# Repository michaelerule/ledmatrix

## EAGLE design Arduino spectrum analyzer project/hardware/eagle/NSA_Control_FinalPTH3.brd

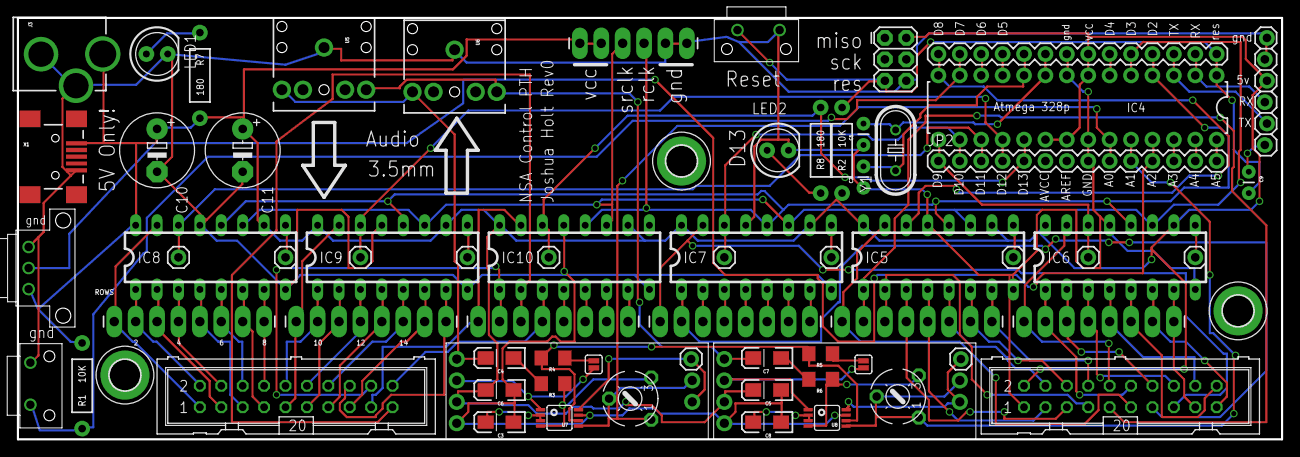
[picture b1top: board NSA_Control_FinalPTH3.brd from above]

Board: 2 copper layers, 150.0 x 50.0 mm, 72 parts (0 on the bottom side), 96 nets.

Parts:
C1, C2: 22pf; CAP-PTH-SMALL
C3, C4, C5, C6, C7, C8: 1uF; EIA3216-KIT
C9: 0.1uF; CAP-PTH-SMALL
C10, C11: E5-8,5
H1, H2, H3: MOUNT-PAD-ROUND3.6; 3,6-PAD
IC4: AVR-MEGA8-PZIF_SOCKET; DIL28-3-ZIF_SOCKET
IC5, IC6, IC7, IC8, IC9, IC10: 74LS595N; DIL16
J1: AVR_SPI_PRG_6PTH; 2X3
J3: POWER_JACKPTH_LOCK; POWER_JACK_PTH_LOCK
JP1, JP2: M14; 1X14
JP4: 1X06_LONGPADS
JP5, JP6, JP7, JP15, JP16, JP17, JP18, JP19, JP20, JP21, JP22, JP23: M01PTH; 1X01
JP8, JP9, JP11, JP12, JP13, JP14: 1X08_LONGPADS
JP10: 1X06_LOCK
LED1, LED2: LED5MM
R1, R2: 10K; AXIAL-0.4
R3, R6: 10K; 1206
R4, R5: 100K; 1206
R7, R8: 180; AXIAL-0.4
SJ1, SJ2: SOLDERJUMPERNC; SJ_2S
SV1, SV2: ML20
TM1, TM2: 200K; 6MM
U5, U6: AUDIO-JACK
U7, U8: LM4889_MSOP; MSOP8
U$1, U$5: TE_RA_SWTICH; TE_RA_SWITCH
U$6, U$7: MD_AMP
U$10: RK09L
X1: USBSMD; USB-MINIB
Y1: HC49U-V

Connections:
6V: R4.2, R5.2, U7.6, U8.6
A0: IC4.23, JP2.9, TM1.A, TM1.S, U7.5, U$6.SP2
A1: IC4.24, JP2.10, TM2.A, TM2.S, U8.5, U$7.SP2
A2: IC4.25, JP2.11, U$10.P$2
A3: IC4.26, JP2.12
A4: IC4.27, JP2.13
A5: IC4.28, JP2.14
BTN: IC4.13, JP1.13, R1.P$1, U$5.P$2
COL1: IC5.15, JP8.1, SV1.11
COL2: IC5.1, JP8.2, SV1.9
COL3: IC5.2, JP8.3, SV1.7
COL4: IC5.3, JP8.4, SV1.5
COL5: IC5.4, JP8.5, SV1.3
COL6: IC5.5, JP8.6, SV1.4
COL7: IC5.6, JP8.7, SV1.6
COL8: IC5.7, JP8.8, SV1.8
COL9: IC6.15, JP9.1, SV1.10
COL10: IC6.1, JP9.2, SV1.12
COL11: IC6.2, JP9.3, SV1.14
COL12: IC6.3, JP9.4, SV1.16
COL13: IC6.4, JP9.5, SV1.18
COL14: IC6.5, JP9.6, SV1.20
COL15: IC6.6, JP9.7, SV1.19
COL16: IC6.7, JP9.8, SV1.17
COL17: IC7.15, JP11.1, SV1.15
COL18: IC7.1, JP11.2, SV1.13
D4: IC4.6, JP1.6
D5: IC4.11, JP1.11
D6: IC4.12, JP1.12
DTR: C9.1, JP10.1
GND: C1.1, C2.1, C3.C, C5.C, C6.C, C8.C, C10.-, C11.-, IC4.8, IC4.22, IC5.8, IC5.13, IC6.8, IC6.13, IC7.8, IC7.13, IC8.8, IC8.13, IC9.8, IC9.13, IC10.8, IC10.13, J1.6, J3.GND, J3.GNDBREAK, JP1.8, JP2.8, JP4.1, JP4.2, JP10.5, JP10.6, LED1.K, LED2.K, SV1.1, U5.SLEEVE, U6.SLEEVE, U7.7, U8.7, U$1.P$1, U$5.P$1, U$6.GND, U$7.GND, U$10.P$1, X1.GND
L_IN: C4.A, U5.TIP, U6.TIP, U$6.AIN
unnamed: IC7.4, JP11.5
unnamed: IC7.5, JP11.6
unnamed: IC7.6, JP11.7
unnamed: IC7.7, JP11.8
unnamed: IC10.4, JP14.5
unnamed: IC10.5, JP14.6
unnamed: LED1.A, R7.P$1
unnamed: LED2.A, R8.P$1
unnamed: IC10.6, JP14.7
unnamed: C8.A, U8.2, U8.3
unnamed: IC5.9, JP5.1
unnamed: IC6.9, JP16.1
unnamed: IC10.7, JP14.8
unnamed: C3.A, U7.2, U7.3
unnamed: R6.1, TM2.E, U8.4
unnamed: R3.1, TM1.E, U7.4
unnamed: C4.C, R3.2
unnamed: C7.C, R6.2
unnamed: R4.1, SJ1.2
unnamed: R5.1, SJ2.2
unnamed: IC7.2, JP11.3
unnamed: IC7.3, JP11.4
unnamed: IC7.9, JP18.1
unnamed: IC8.9, JP20.1
unnamed: IC9.9, JP22.1
RCLK: IC4.4, IC5.12, IC6.12, IC7.12, IC8.12, IC9.12, IC10.12, JP1.4, JP4.3
RES: C9.2, IC4.1, J1.5, JP1.1, R2.P$1, U$1.P$2
ROW1: IC8.15, JP12.1, SV2.1
ROW2: IC8.1, JP12.2, SV2.2
ROW3: IC8.2, JP12.3, SV2.3
ROW4: IC8.3, JP12.4, SV2.4
ROW5: IC8.4, JP12.5, SV2.5
ROW6: IC8.5, JP12.6, SV2.6
ROW7: IC8.6, JP12.7, SV2.7
ROW8: IC8.7, JP12.8, SV2.8
ROW9: IC9.15, JP13.1, SV2.9
ROW10: IC9.1, JP13.2, SV2.10
ROW11: IC9.2, JP13.3, SV2.11
ROW12: IC9.3, JP13.4, SV2.12
ROW13: IC9.4, JP13.5, SV2.13
ROW14: IC9.5, JP13.6, SV2.14
ROW15: IC9.6, JP13.7, SV2.15
ROW16: IC9.7, JP13.8, SV2.16
ROW17: IC10.15, JP14.1, SV2.17
ROW18: IC10.1, JP14.2, SV2.18
ROW19: IC10.2, JP14.3, SV2.19
ROW20: IC10.3, JP14.4, SV2.20
RX: IC4.2, JP1.2, JP10.3
R_IN: C7.A, U5.RING, U6.RING, U$7.AIN
SP1: JP6.1, U7.8, U$6.SP1
SP1_2: JP7.1, U8.8, U$7.SP1
SR1_SER: IC4.14, IC5.14, JP1.14
SR2_SER: IC4.15, IC6.14, JP2.1, JP15.1
SR3_SER: IC4.16, IC7.14, JP2.2, JP17.1
SR4_SER: IC4.17, IC8.14, JP2.3, JP19.1
SR5_SER: IC4.18, IC9.14, JP2.4, JP21.1
SR6_SER: IC4.19, IC10.14, JP2.5, JP23.1, R8.P$2
SRCLK: IC4.5, IC5.11, IC6.11, IC7.11, IC8.11, IC9.11, IC10.11, JP1.5, JP4.4
STDN: SJ1.1, U7.1, U$6.STDN
STDN2: SJ2.1, U8.1, U$7.STDN
TX: IC4.3, JP1.3, JP10.2
VCC: C5.A, C6.A, C10.+, C11.+, IC4.7, IC4.20, IC4.21, IC5.10, IC5.16, IC6.10, IC6.16, IC7.10, IC7.16, IC8.10, IC8.16, IC9.10, IC9.16, IC10.10, IC10.16, J1.2, J3.PWR, JP1.7, JP4.5, JP4.6, JP10.4, R1.P$2, R2.P$2, R7.P$2, SV1.2, U$6.5V, U$7.5V, U$10.P$3, X1.VBUS
XTAL1: C1.2, IC4.9, JP1.9, Y1.2
XTAL2: C2.2, IC4.10, JP1.10, Y1.1

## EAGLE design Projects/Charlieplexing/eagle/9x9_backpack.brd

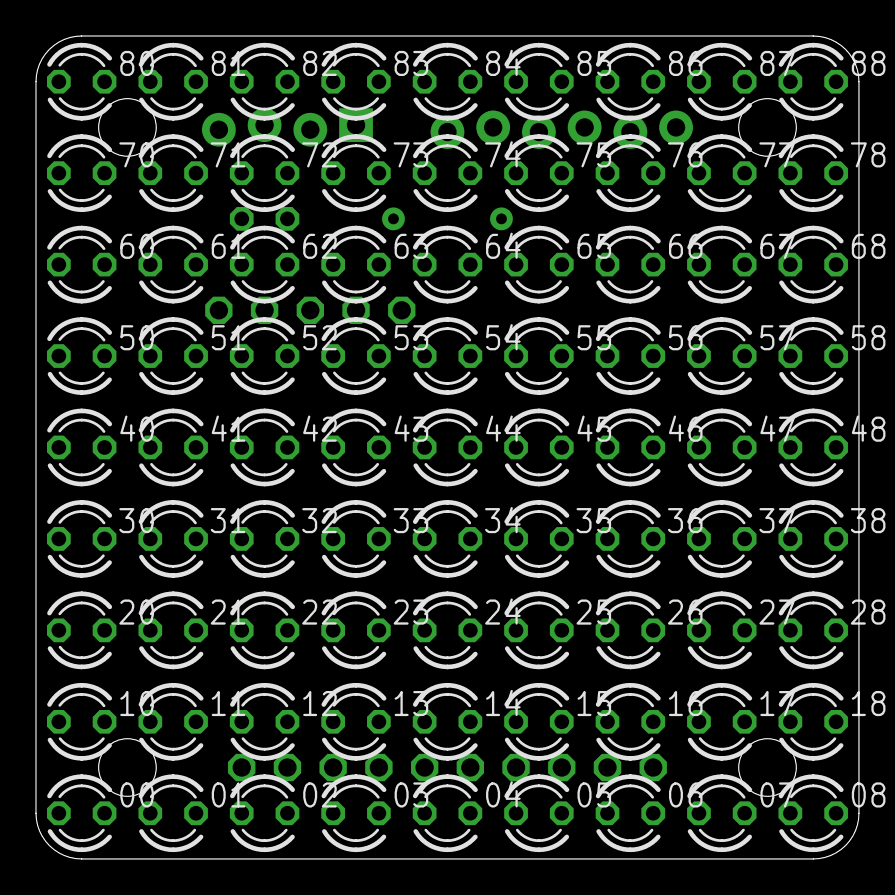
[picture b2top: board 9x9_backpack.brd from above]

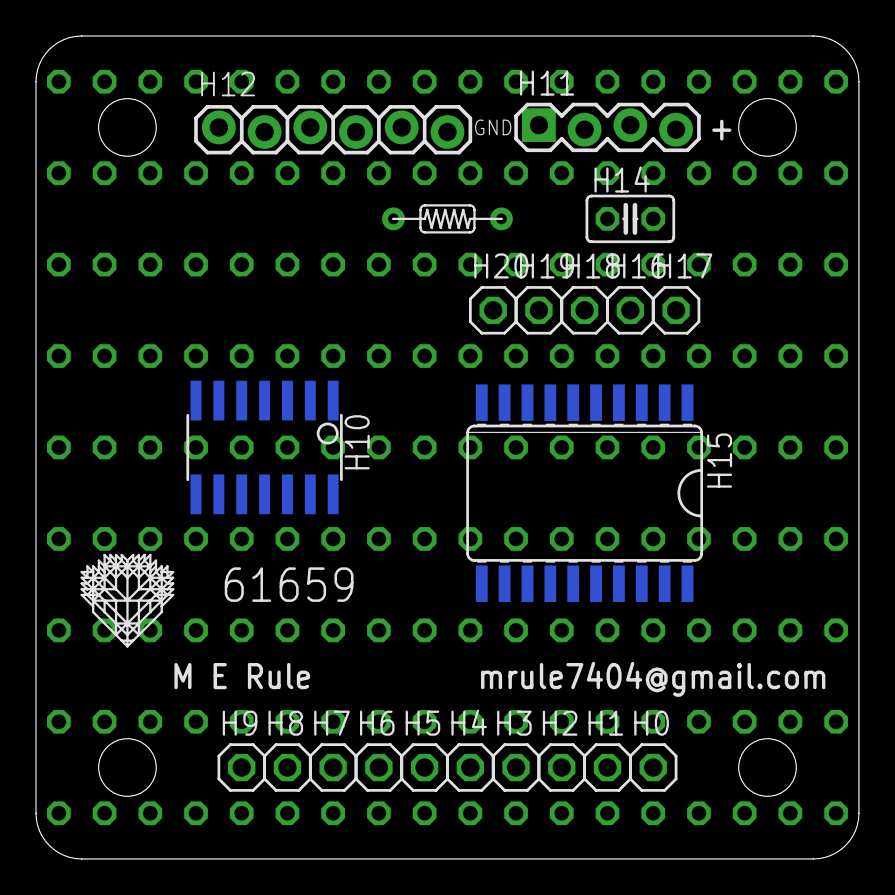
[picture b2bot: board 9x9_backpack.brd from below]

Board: 2 copper layers, 45.7 x 45.7 mm, 103 parts (22 on the bottom side), 20 nets, no tracks yet.

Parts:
00, 01, 02, 03, 04, 05, 06, 07, 08, 10, 11, 12, 13, 14, 15, 16, 17, 18, 20, 21, 22, 23, 24, 25, 26, 27, 28, 30, 31, 32, 33, 34, 35, 36, 37, 38, 40, 41, 42, 43, 44, 45, 46, 47, 48, 50, 51, 52, 53, 54, 55, 56, 57, 58, 60, 61, 62, 63, 64, 65, 66, 67, 68, 70, 71, 72, 73, 74, 75, 76, 77, 78, 80, 81, 82, 83, 84, 85, 86, 87, 88: LED3MM
H0, H1, H2, H3, H4, H5, H6, H7, H8, H9, H16, H17, H18, H19, H20: 1X01
H10: SOIC14
H11: 1X04_LOCK
H12: 1X06_LOCK
H13: R-6
H14: C025-025X050
H15: SO20L
H21: LOGO

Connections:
D: 00.A, 11.A, 22.A, 33.A, 44.A, 55.A, 66.A, 77.A, 88.A, H9.1, H10.8, H12.5, H15.18
S0: 00.K, 01.A, 02.A, 03.A, 04.A, 05.A, 06.A, 07.A, 08.A, 10.K, 20.K, 30.K, 40.K, 50.K, 60.K, 70.K, 80.K, H0.1, H10.3, H15.9
S1: 01.K, 10.A, 11.K, 12.A, 13.A, 14.A, 15.A, 16.A, 17.A, 18.A, 21.K, 31.K, 41.K, 51.K, 61.K, 71.K, 81.K, H1.1, H10.5, H15.16
S2: 02.K, 12.K, 20.A, 21.A, 22.K, 23.A, 24.A, 25.A, 26.A, 27.A, 28.A, 32.K, 42.K, 52.K, 62.K, 72.K, 82.K, H2.1, H10.6, H15.15
S3: 03.K, 13.K, 23.K, 30.A, 31.A, 32.A, 33.K, 34.A, 35.A, 36.A, 37.A, 38.A, 43.K, 53.K, 63.K, 73.K, 83.K, H3.1, H10.7, H12.1, H15.17
S4: 04.K, 14.K, 24.K, 34.K, 40.A, 41.A, 42.A, 43.A, 44.K, 45.A, 46.A, 47.A, 48.A, 54.K, 64.K, 74.K, 84.K, H4.1, H10.13, H15.14
S5: 05.K, 15.K, 25.K, 35.K, 45.K, 50.A, 51.A, 52.A, 53.A, 54.A, 55.K, 56.A, 57.A, 58.A, 65.K, 75.K, 85.K, H5.1, H10.12, H15.13
S6: 06.K, 16.K, 26.K, 36.K, 46.K, 56.K, 60.A, 61.A, 62.A, 63.A, 64.A, 65.A, 66.K, 67.A, 68.A, 76.K, 86.K, H6.1, H10.11, H15.12
S7: 07.K, 17.K, 27.K, 37.K, 47.K, 57.K, 67.K, 70.A, 71.A, 72.A, 73.A, 74.A, 75.A, 76.A, 77.K, 78.A, 87.K, H7.1, H10.10, H15.11
S8: 08.K, 18.K, 28.K, 38.K, 48.K, 58.K, 68.K, 78.K, 80.A, 81.A, 82.A, 83.A, 84.A, 85.A, 86.A, 87.A, 88.K, H8.1, H10.9, H12.2, H15.19
S$1: H10.14, H11.1, H12.6, H14.1, H15.10
S$2: H10.1, H11.4, H12.4, H13.P$2, H14.2, H15.20
S$3: H10.4, H12.3, H13.P$1, H15.1
S$4: H10.2, H11.2, H15.2
S$5: H11.3, H15.3
S$6: H15.8, H20.1
S$7: H15.7, H19.1
S$8: H15.6, H18.1
S$9: H15.5, H16.1
S$10: H15.4, H17.1

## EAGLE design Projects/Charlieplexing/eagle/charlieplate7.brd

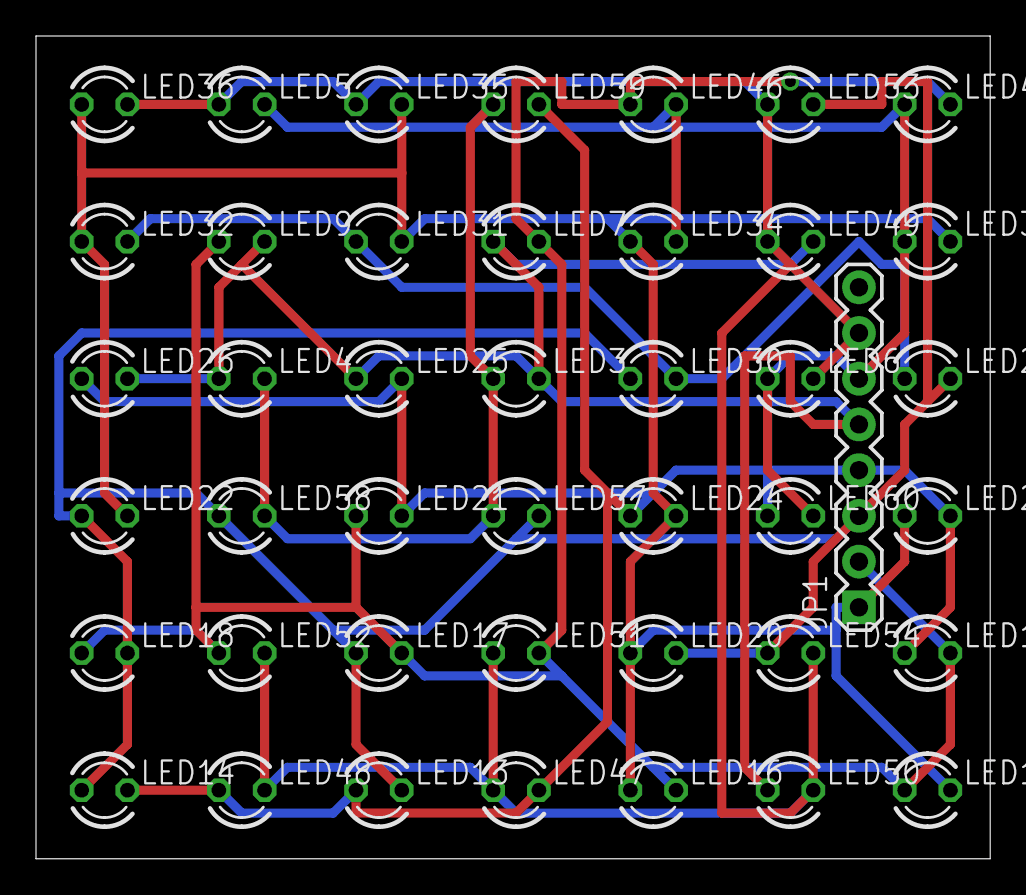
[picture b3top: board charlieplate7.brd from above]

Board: 2 copper layers, 53.0 x 45.7 mm, 43 parts (0 on the bottom side), 8 nets.

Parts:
JP1: 1X08
LED3, LED4, LED5, LED6, LED7, LED9, LED13, LED14, LED15, LED16, LED17, LED18, LED19, LED20, LED21, LED22, LED23, LED24, LED25, LED26, LED29, LED30, LED31, LED32, LED33, LED34, LED35, LED36, LED45, LED46, LED47, LED48, LED49, LED50, LED51, LED52, LED53, LED54, LED57, LED58, LED59, LED60: LED3MM

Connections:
unnamed: LED29.A, LED30.K, LED31.A, LED32.K
unnamed: JP1.1, LED15.K, LED16.A, LED20.A, LED22.K, LED23.A, LED24.K, LED31.K, LED32.A, LED33.K, LED34.A, LED35.K, LED36.A
unnamed: JP1.3, LED13.K, LED14.A, LED17.A, LED18.K, LED20.K, LED22.A, LED29.K, LED30.A, LED53.K, LED54.A, LED57.K, LED58.A
unnamed: JP1.6, LED3.A, LED4.K, LED5.K, LED6.A, LED33.A, LED34.K, LED45.A, LED46.K, LED57.A, LED58.K, LED59.A, LED60.K
unnamed: JP1.4, LED13.A, LED14.K, LED19.A, LED21.K, LED23.K, LED24.A, LED25.K, LED26.A, LED47.K, LED48.A, LED59.K, LED60.A
unnamed: JP1.5, LED3.K, LED4.A, LED7.A, LED9.K, LED25.A, LED26.K, LED49.K, LED50.A
unnamed: JP1.7, LED5.A, LED6.K, LED35.A, LED36.K, LED47.A, LED48.K, LED49.A, LED50.K, LED51.A, LED52.K, LED53.A, LED54.K
unnamed: JP1.2, LED7.K, LED9.A, LED15.A, LED16.K, LED17.K, LED18.A, LED19.K, LED21.A, LED45.K, LED46.A, LED51.K, LED52.A

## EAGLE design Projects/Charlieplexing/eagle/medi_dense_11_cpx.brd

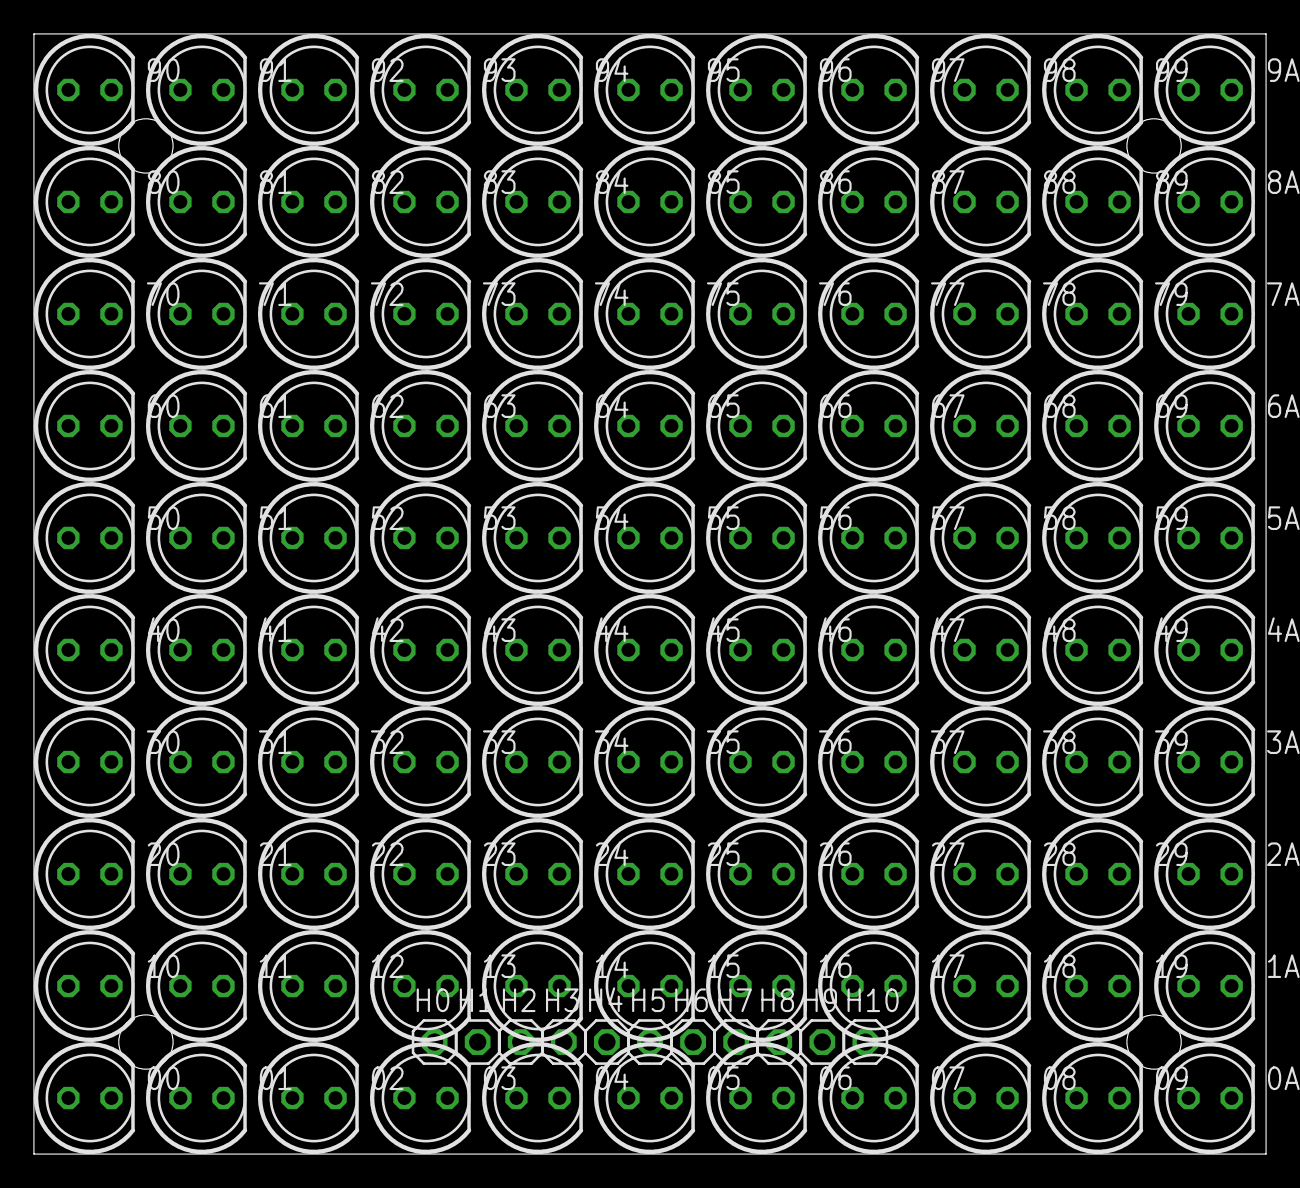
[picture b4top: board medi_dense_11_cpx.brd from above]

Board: 2 copper layers, 72.6 x 66.0 mm, 121 parts (0 on the bottom side), 11 nets, no tracks yet.

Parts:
00, 0A, 01, 1A, 02, 2A, 03, 3A, 04, 4A, 05, 5A, 06, 6A, 07, 7A, 08, 8A, 09, 9A, 10, 11, 12, 13, 14, 15, 16, 17, 18, 19, 20, 21, 22, 23, 24, 25, 26, 27, 28, 29, 30, 31, 32, 33, 34, 35, 36, 37, 38, 39, 40, 41, 42, 43, 44, 45, 46, 47, 48, 49, 50, 51, 52, 53, 54, 55, 56, 57, 58, 59, 60, 61, 62, 63, 64, 65, 66, 67, 68, 69, 70, 71, 72, 73, 74, 75, 76, 77, 78, 79, 80, 81, 82, 83, 84, 85, 86, 87, 88, 89, 90, 91, 92, 93, 94, 95, 96, 97, 98, 99: LED5MM
H0, H1, H2, H3, H4, H5, H6, H7, H8, H9, H10: 1X01

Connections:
D: 00.A, 0A.K, 1A.K, 2A.K, 3A.K, 4A.K, 5A.K, 6A.K, 7A.K, 8A.K, 9A.K, 11.A, 22.A, 33.A, 44.A, 55.A, 66.A, 77.A, 88.A, 99.A, H10.1
S0: 00.K, 0A.A, 01.A, 02.A, 03.A, 04.A, 05.A, 06.A, 07.A, 08.A, 09.A, 10.K, 20.K, 30.K, 40.K, 50.K, 60.K, 70.K, 80.K, 90.K, H0.1
S1: 01.K, 1A.A, 10.A, 11.K, 12.A, 13.A, 14.A, 15.A, 16.A, 17.A, 18.A, 19.A, 21.K, 31.K, 41.K, 51.K, 61.K, 71.K, 81.K, 91.K, H1.1
S2: 02.K, 2A.A, 12.K, 20.A, 21.A, 22.K, 23.A, 24.A, 25.A, 26.A, 27.A, 28.A, 29.A, 32.K, 42.K, 52.K, 62.K, 72.K, 82.K, 92.K, H2.1
S3: 03.K, 3A.A, 13.K, 23.K, 30.A, 31.A, 32.A, 33.K, 34.A, 35.A, 36.A, 37.A, 38.A, 39.A, 43.K, 53.K, 63.K, 73.K, 83.K, 93.K, H3.1
S4: 04.K, 4A.A, 14.K, 24.K, 34.K, 40.A, 41.A, 42.A, 43.A, 44.K, 45.A, 46.A, 47.A, 48.A, 49.A, 54.K, 64.K, 74.K, 84.K, 94.K, H4.1
S5: 05.K, 5A.A, 15.K, 25.K, 35.K, 45.K, 50.A, 51.A, 52.A, 53.A, 54.A, 55.K, 56.A, 57.A, 58.A, 59.A, 65.K, 75.K, 85.K, 95.K, H5.1
S6: 06.K, 6A.A, 16.K, 26.K, 36.K, 46.K, 56.K, 60.A, 61.A, 62.A, 63.A, 64.A, 65.A, 66.K, 67.A, 68.A, 69.A, 76.K, 86.K, 96.K, H6.1
S7: 07.K, 7A.A, 17.K, 27.K, 37.K, 47.K, 57.K, 67.K, 70.A, 71.A, 72.A, 73.A, 74.A, 75.A, 76.A, 77.K, 78.A, 79.A, 87.K, 97.K, H7.1
S8: 08.K, 8A.A, 18.K, 28.K, 38.K, 48.K, 58.K, 68.K, 78.K, 80.A, 81.A, 82.A, 83.A, 84.A, 85.A, 86.A, 87.A, 88.K, 89.A, 98.K, H8.1
S9: 09.K, 9A.A, 19.K, 29.K, 39.K, 49.K, 59.K, 69.K, 79.K, 89.K, 90.A, 91.A, 92.A, 93.A, 94.A, 95.A, 96.A, 97.A, 98.A, 99.K, H9.1

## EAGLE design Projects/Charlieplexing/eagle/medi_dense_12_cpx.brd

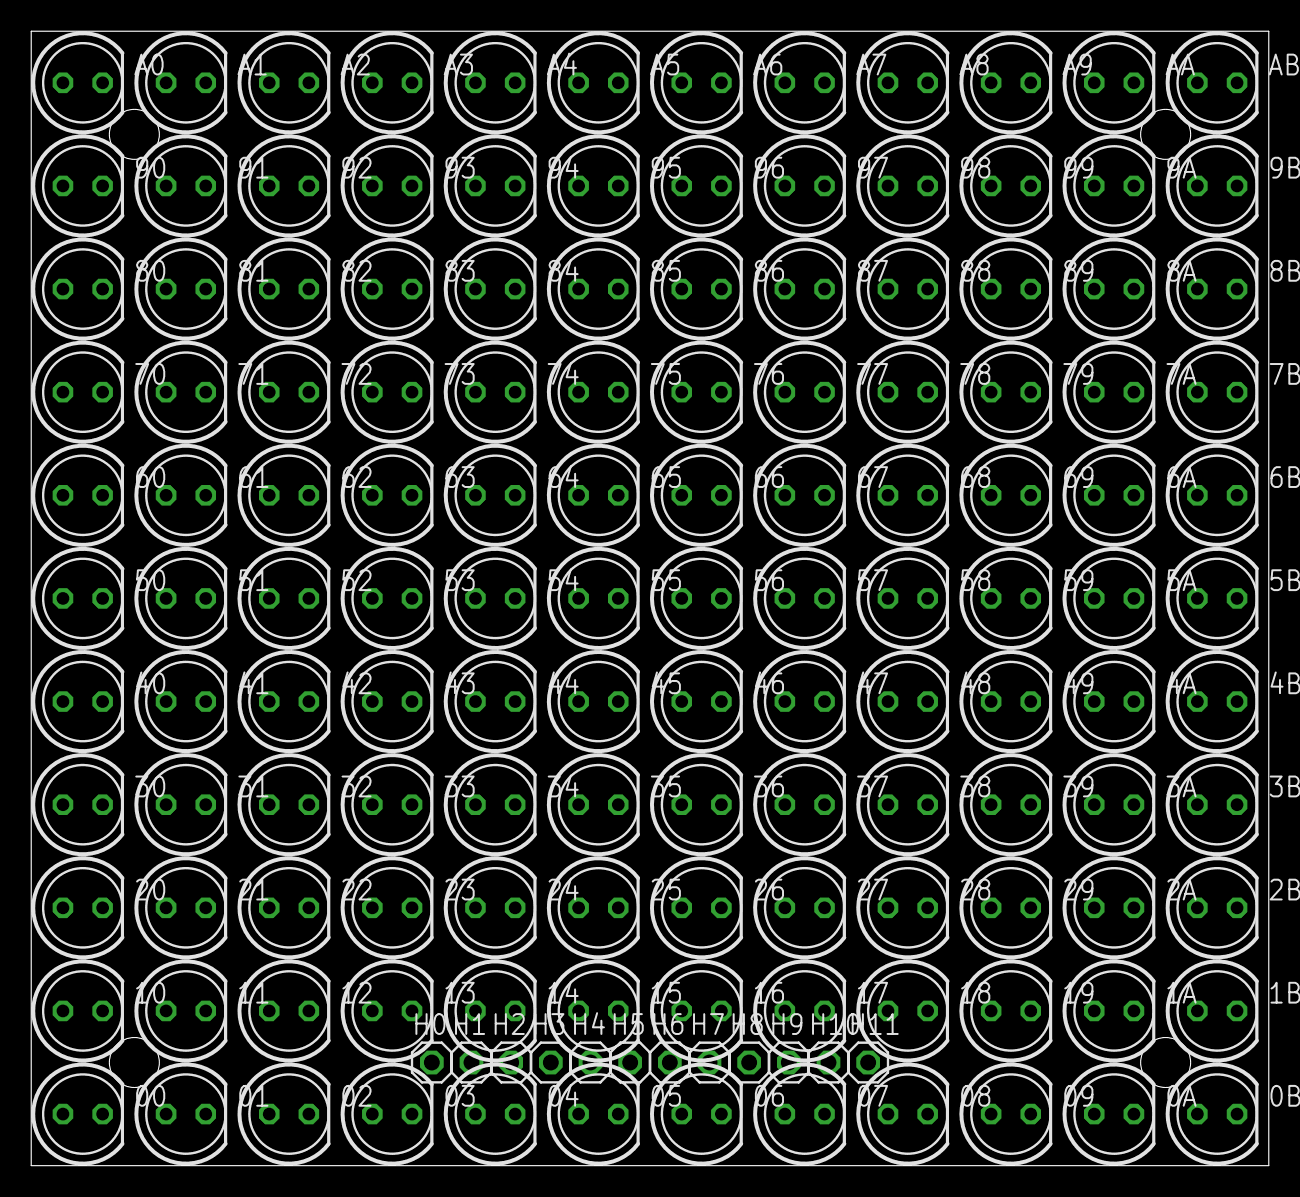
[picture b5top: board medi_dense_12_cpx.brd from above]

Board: 2 copper layers, 79.2 x 72.6 mm, 144 parts (0 on the bottom side), 12 nets, no tracks yet.

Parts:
00, 0A, 0B, 01, 1A, 1B, 02, 2A, 2B, 03, 3A, 3B, 04, 4A, 4B, 05, 5A, 5B, 06, 6A, 6B, 07, 7A, 7B, 08, 8A, 8B, 09, 9A, 9B, 10, 11, 12, 13, 14, 15, 16, 17, 18, 19, 20, 21, 22, 23, 24, 25, 26, 27, 28, 29, 30, 31, 32, 33, 34, 35, 36, 37, 38, 39, 40, 41, 42, 43, 44, 45, 46, 47, 48, 49, 50, 51, 52, 53, 54, 55, 56, 57, 58, 59, 60, 61, 62, 63, 64, 65, 66, 67, 68, 69, 70, 71, 72, 73, 74, 75, 76, 77, 78, 79, 80, 81, 82, 83, 84, 85, 86, 87, 88, 89, 90, 91, 92, 93, 94, 95, 96, 97, 98, 99: LED5MM
A0, A1, A2, A3, A4, A5, A6, A7, A8, A9: LED5MM
AA: LED5MM
AB: LED5MM
H0, H1, H2, H3, H4, H5, H6, H7, H8, H9, H10, H11: 1X01

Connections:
D: 00.A, 0B.K, 1B.K, 2B.K, 3B.K, 4B.K, 5B.K, 6B.K, 7B.K, 8B.K, 9B.K, 11.A, 22.A, 33.A, 44.A, 55.A, 66.A, 77.A, 88.A, 99.A, AA.A, AB.K, H11.1
S0: 00.K, 0A.A, 0B.A, 01.A, 02.A, 03.A, 04.A, 05.A, 06.A, 07.A, 08.A, 09.A, 10.K, 20.K, 30.K, 40.K, 50.K, 60.K, 70.K, 80.K, 90.K, A0.K, H0.1
S1: 01.K, 1A.A, 1B.A, 10.A, 11.K, 12.A, 13.A, 14.A, 15.A, 16.A, 17.A, 18.A, 19.A, 21.K, 31.K, 41.K, 51.K, 61.K, 71.K, 81.K, 91.K, A1.K, H1.1
S2: 02.K, 2A.A, 2B.A, 12.K, 20.A, 21.A, 22.K, 23.A, 24.A, 25.A, 26.A, 27.A, 28.A, 29.A, 32.K, 42.K, 52.K, 62.K, 72.K, 82.K, 92.K, A2.K, H2.1
S3: 03.K, 3A.A, 3B.A, 13.K, 23.K, 30.A, 31.A, 32.A, 33.K, 34.A, 35.A, 36.A, 37.A, 38.A, 39.A, 43.K, 53.K, 63.K, 73.K, 83.K, 93.K, A3.K, H3.1
S4: 04.K, 4A.A, 4B.A, 14.K, 24.K, 34.K, 40.A, 41.A, 42.A, 43.A, 44.K, 45.A, 46.A, 47.A, 48.A, 49.A, 54.K, 64.K, 74.K, 84.K, 94.K, A4.K, H4.1
S5: 05.K, 5A.A, 5B.A, 15.K, 25.K, 35.K, 45.K, 50.A, 51.A, 52.A, 53.A, 54.A, 55.K, 56.A, 57.A, 58.A, 59.A, 65.K, 75.K, 85.K, 95.K, A5.K, H5.1
S6: 06.K, 6A.A, 6B.A, 16.K, 26.K, 36.K, 46.K, 56.K, 60.A, 61.A, 62.A, 63.A, 64.A, 65.A, 66.K, 67.A, 68.A, 69.A, 76.K, 86.K, 96.K, A6.K, H6.1
S7: 07.K, 7A.A, 7B.A, 17.K, 27.K, 37.K, 47.K, 57.K, 67.K, 70.A, 71.A, 72.A, 73.A, 74.A, 75.A, 76.A, 77.K, 78.A, 79.A, 87.K, 97.K, A7.K, H7.1
S8: 08.K, 8A.A, 8B.A, 18.K, 28.K, 38.K, 48.K, 58.K, 68.K, 78.K, 80.A, 81.A, 82.A, 83.A, 84.A, 85.A, 86.A, 87.A, 88.K, 89.A, 98.K, A8.K, H8.1
S9: 09.K, 9A.A, 9B.A, 19.K, 29.K, 39.K, 49.K, 59.K, 69.K, 79.K, 89.K, 90.A, 91.A, 92.A, 93.A, 94.A, 95.A, 96.A, 97.A, 98.A, 99.K, A9.K, H9.1
S10: 0A.K, 1A.K, 2A.K, 3A.K, 4A.K, 5A.K, 6A.K, 7A.K, 8A.K, 9A.K, A0.A, A1.A, A2.A, A3.A, A4.A, A5.A, A6.A, A7.A, A8.A, A9.A, AA.K, AB.A, H10.1

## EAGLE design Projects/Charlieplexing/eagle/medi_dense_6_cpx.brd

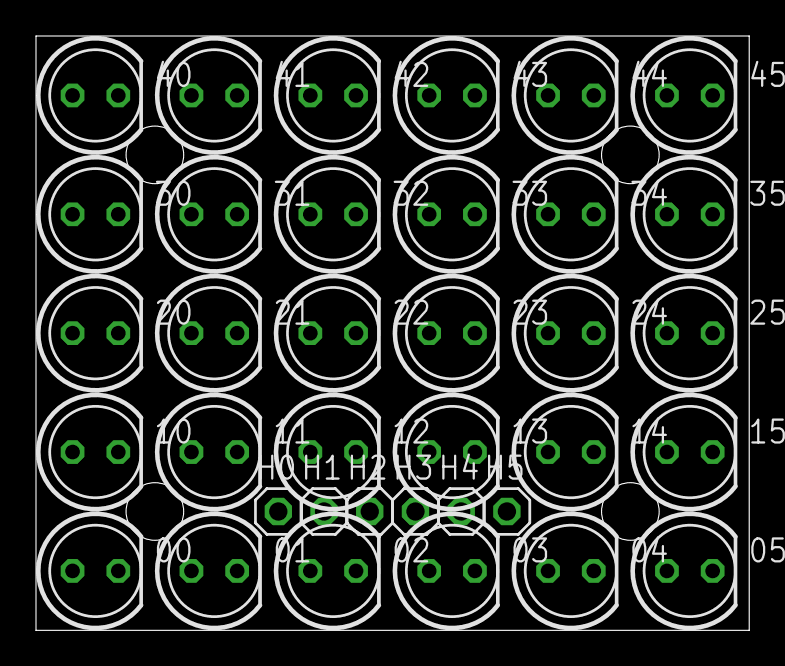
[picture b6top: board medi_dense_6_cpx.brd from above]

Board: 2 copper layers, 39.6 x 33.0 mm, 36 parts (0 on the bottom side), 6 nets, no tracks yet.

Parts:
00, 01, 02, 03, 04, 05, 10, 11, 12, 13, 14, 15, 20, 21, 22, 23, 24, 25, 30, 31, 32, 33, 34, 35, 40, 41, 42, 43, 44, 45: LED5MM
H0, H1, H2, H3, H4, H5: 1X01

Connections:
D: 00.A, 05.K, 11.A, 15.K, 22.A, 25.K, 33.A, 35.K, 44.A, 45.K, H5.1
S0: 00.K, 01.A, 02.A, 03.A, 04.A, 05.A, 10.K, 20.K, 30.K, 40.K, H0.1
S1: 01.K, 10.A, 11.K, 12.A, 13.A, 14.A, 15.A, 21.K, 31.K, 41.K, H1.1
S2: 02.K, 12.K, 20.A, 21.A, 22.K, 23.A, 24.A, 25.A, 32.K, 42.K, H2.1
S3: 03.K, 13.K, 23.K, 30.A, 31.A, 32.A, 33.K, 34.A, 35.A, 43.K, H3.1
S4: 04.K, 14.K, 24.K, 34.K, 40.A, 41.A, 42.A, 43.A, 44.K, 45.A, H4.1

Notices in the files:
parts and their libraries:
sparkFun: Licensing: CC v3.0 Share-Alike You are welcome to use this library for commercial purposes.
